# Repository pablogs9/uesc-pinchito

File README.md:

# uESC pinchito edition

An evolution of the uESC from the
[rcgroups.com forum](https://www.rcgroups.com/forums/showthread.php?2971342-uESC-World-smallest-1S-BLHeli_S-ESC)
by user [nppc](https://github.com/nppc).
Redesign by [Pablo Garrido](https://github.com/pablogs9).

Components are only on the top face for SMT.

Not optimized by size or weight yet.

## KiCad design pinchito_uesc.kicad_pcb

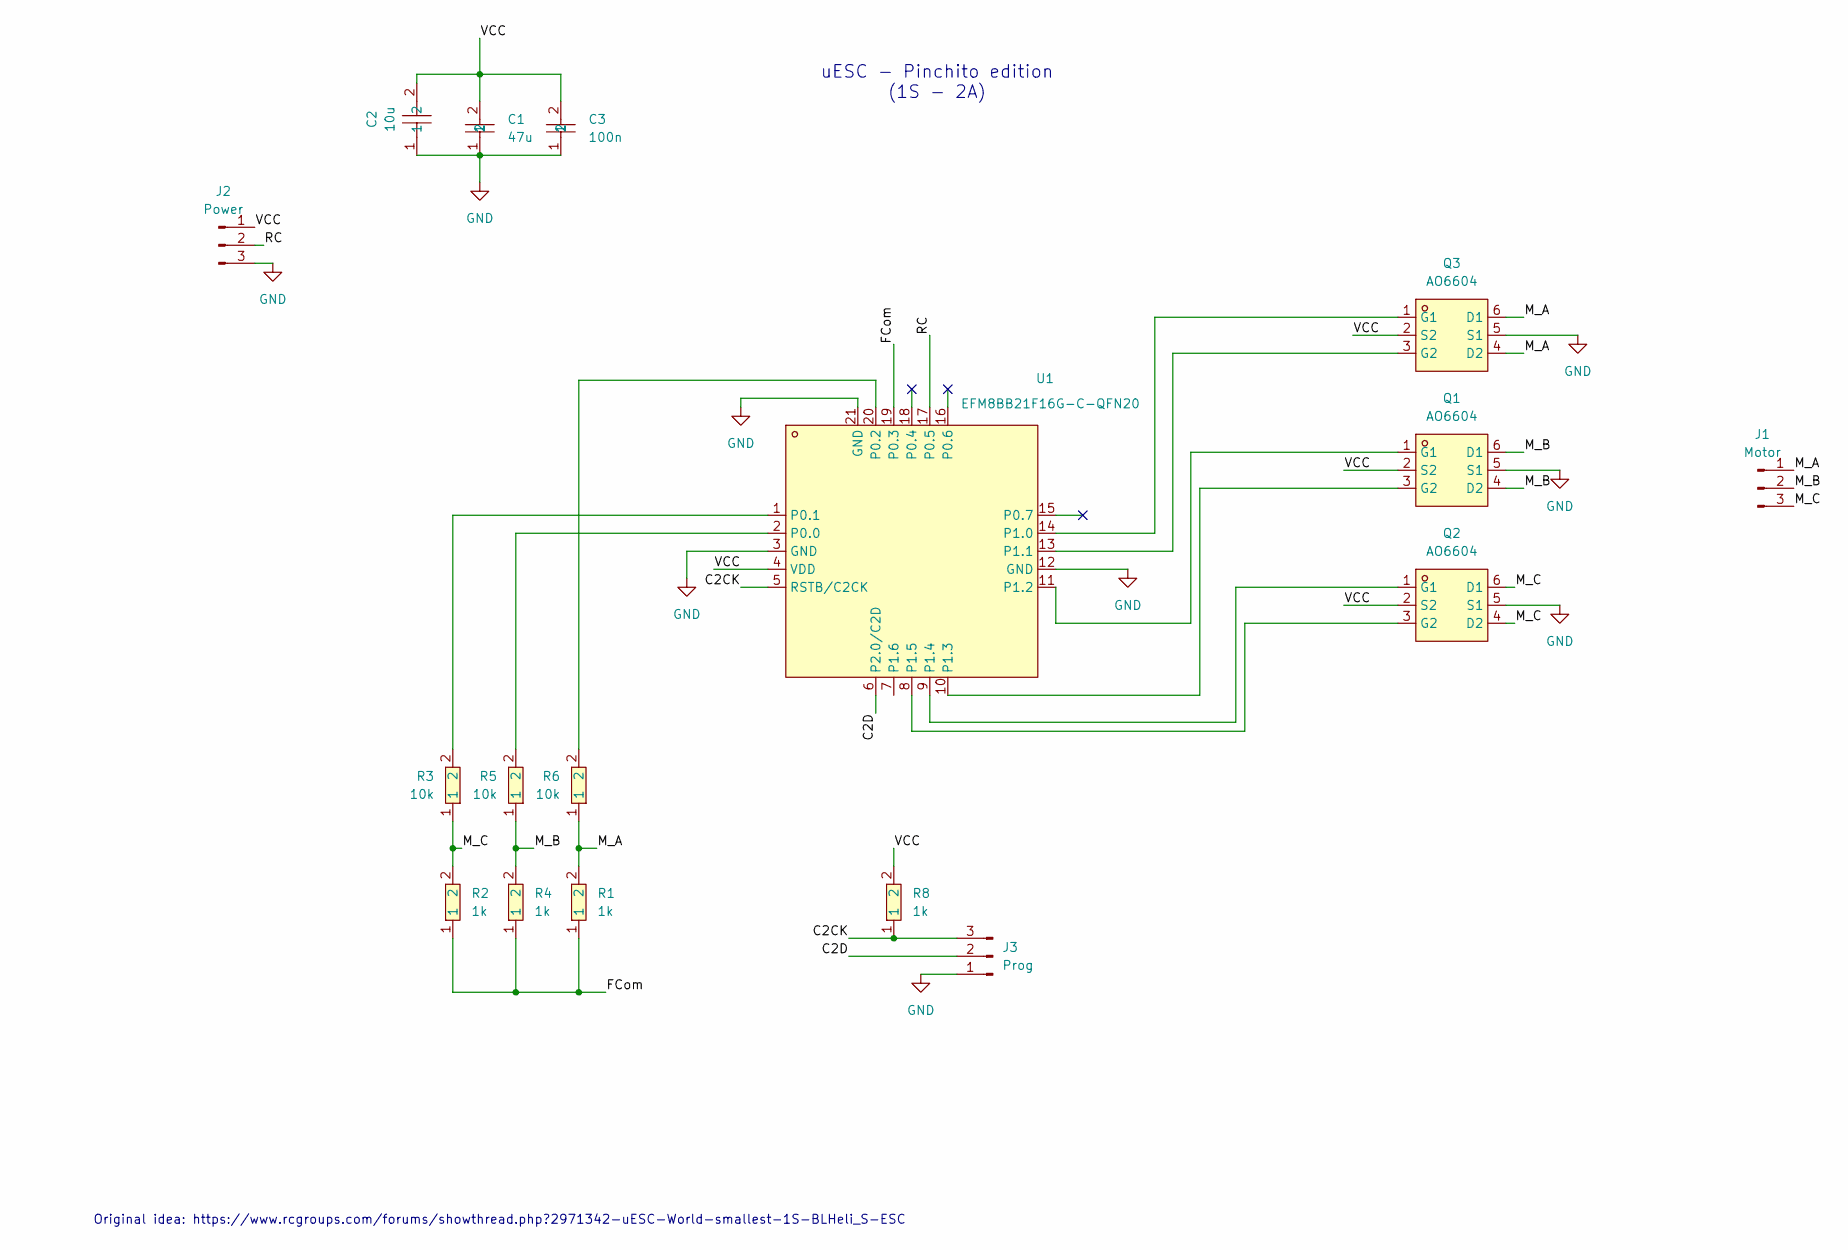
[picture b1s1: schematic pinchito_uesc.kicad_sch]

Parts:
C1: 47u; C0805; LCSC Part C16780
C2: 10u; C0805; LCSC Part C15850
C3: 100n; C0805; LCSC Part C28233
J1: Motor; PinHeader_1x03_P2.00mm_Vertical
J2: Power; PinHeader_1x03_P2.00mm_Vertical
J3: Prog; PinHeader_1x03_P2.00mm_Vertical
Q1, Q2, Q3: AO6604; TSOP-6_L3.0-W1.5-P0.95-LS2.8-BR; LCSC Part C47744
R1, R2, R4, R8: 1k; R0603; LCSC Part C21190
R3, R5, R6: 10k; R0603; LCSC Part C25804
U1: EFM8BB21F16G-C-QFN20; QFN-20_L3.0-W3.0-P0.50-BL-EP1.7_EFM8BB21F16G; LCSC Part C80713

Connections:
/C2CK: J3.3, R8.1, U1.5 (RSTB/C2CK)
/C2D: J3.2, U1.6 (P2.0/C2D)
/FCom: R1.1, R2.1, R4.1, U1.19 (P0.3)
/M_A: J1.1, Q3.4 (D2), Q3.6 (D1), R1.2, R6.1
/M_B: J1.2, Q1.4 (D2), Q1.6 (D1), R4.2, R5.1
/M_C: J1.3, Q2.4 (D2), Q2.6 (D1), R2.2, R3.1
/RC: J2.2, U1.17 (P0.5)
/VCC: C1.2, C2.2, C3.2, J2.1, Q1.2 (S2), Q2.2 (S2), Q3.2 (S2), R8.2, U1.4 (VDD)
GND: C1.1, C2.1, C3.1, J2.3, J3.1, Q1.5 (S1), Q2.5 (S1), Q3.5 (S1), U1.3 (GND), U1.12 (GND), U1.21 (GND)
unnamed: Q1.1 (G1), U1.11 (P1.2)
unnamed: Q1.3 (G2), U1.10 (P1.3)
unnamed: Q2.1 (G1), U1.9 (P1.4)
unnamed: Q2.3 (G2), U1.8 (P1.5)
unnamed: Q3.1 (G1), U1.14 (P1.0)
unnamed: Q3.3 (G2), U1.13 (P1.1)
unnamed: R5.2, U1.2 (P0.0)
unnamed: R3.2, U1.1 (P0.1)
unnamed: R6.2, U1.20 (P0.2)

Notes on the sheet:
uESC - Pinchito edition (1S - 2A)
Original idea: https://www.rcgroups.com/forums/showthread.php?2971342-uESC-World-smallest-1S-BLHeli_S-ESC

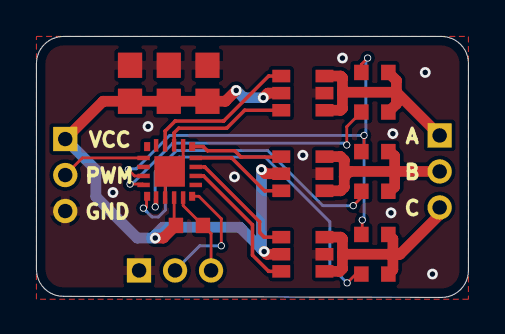
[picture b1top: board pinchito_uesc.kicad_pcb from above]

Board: 2 copper layers, 24.0 x 14.5 mm, 17 parts (0 on the bottom side), 18 nets.

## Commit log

2025-01-18 Initial
2025-01-18 Add Fab V1
2025-01-18 Improved Readme
2025-01-29 Bump design to new MOSFETs
2025-01-29 Round Corners
2025-01-30 Fix Via size to .3/.4 mm
